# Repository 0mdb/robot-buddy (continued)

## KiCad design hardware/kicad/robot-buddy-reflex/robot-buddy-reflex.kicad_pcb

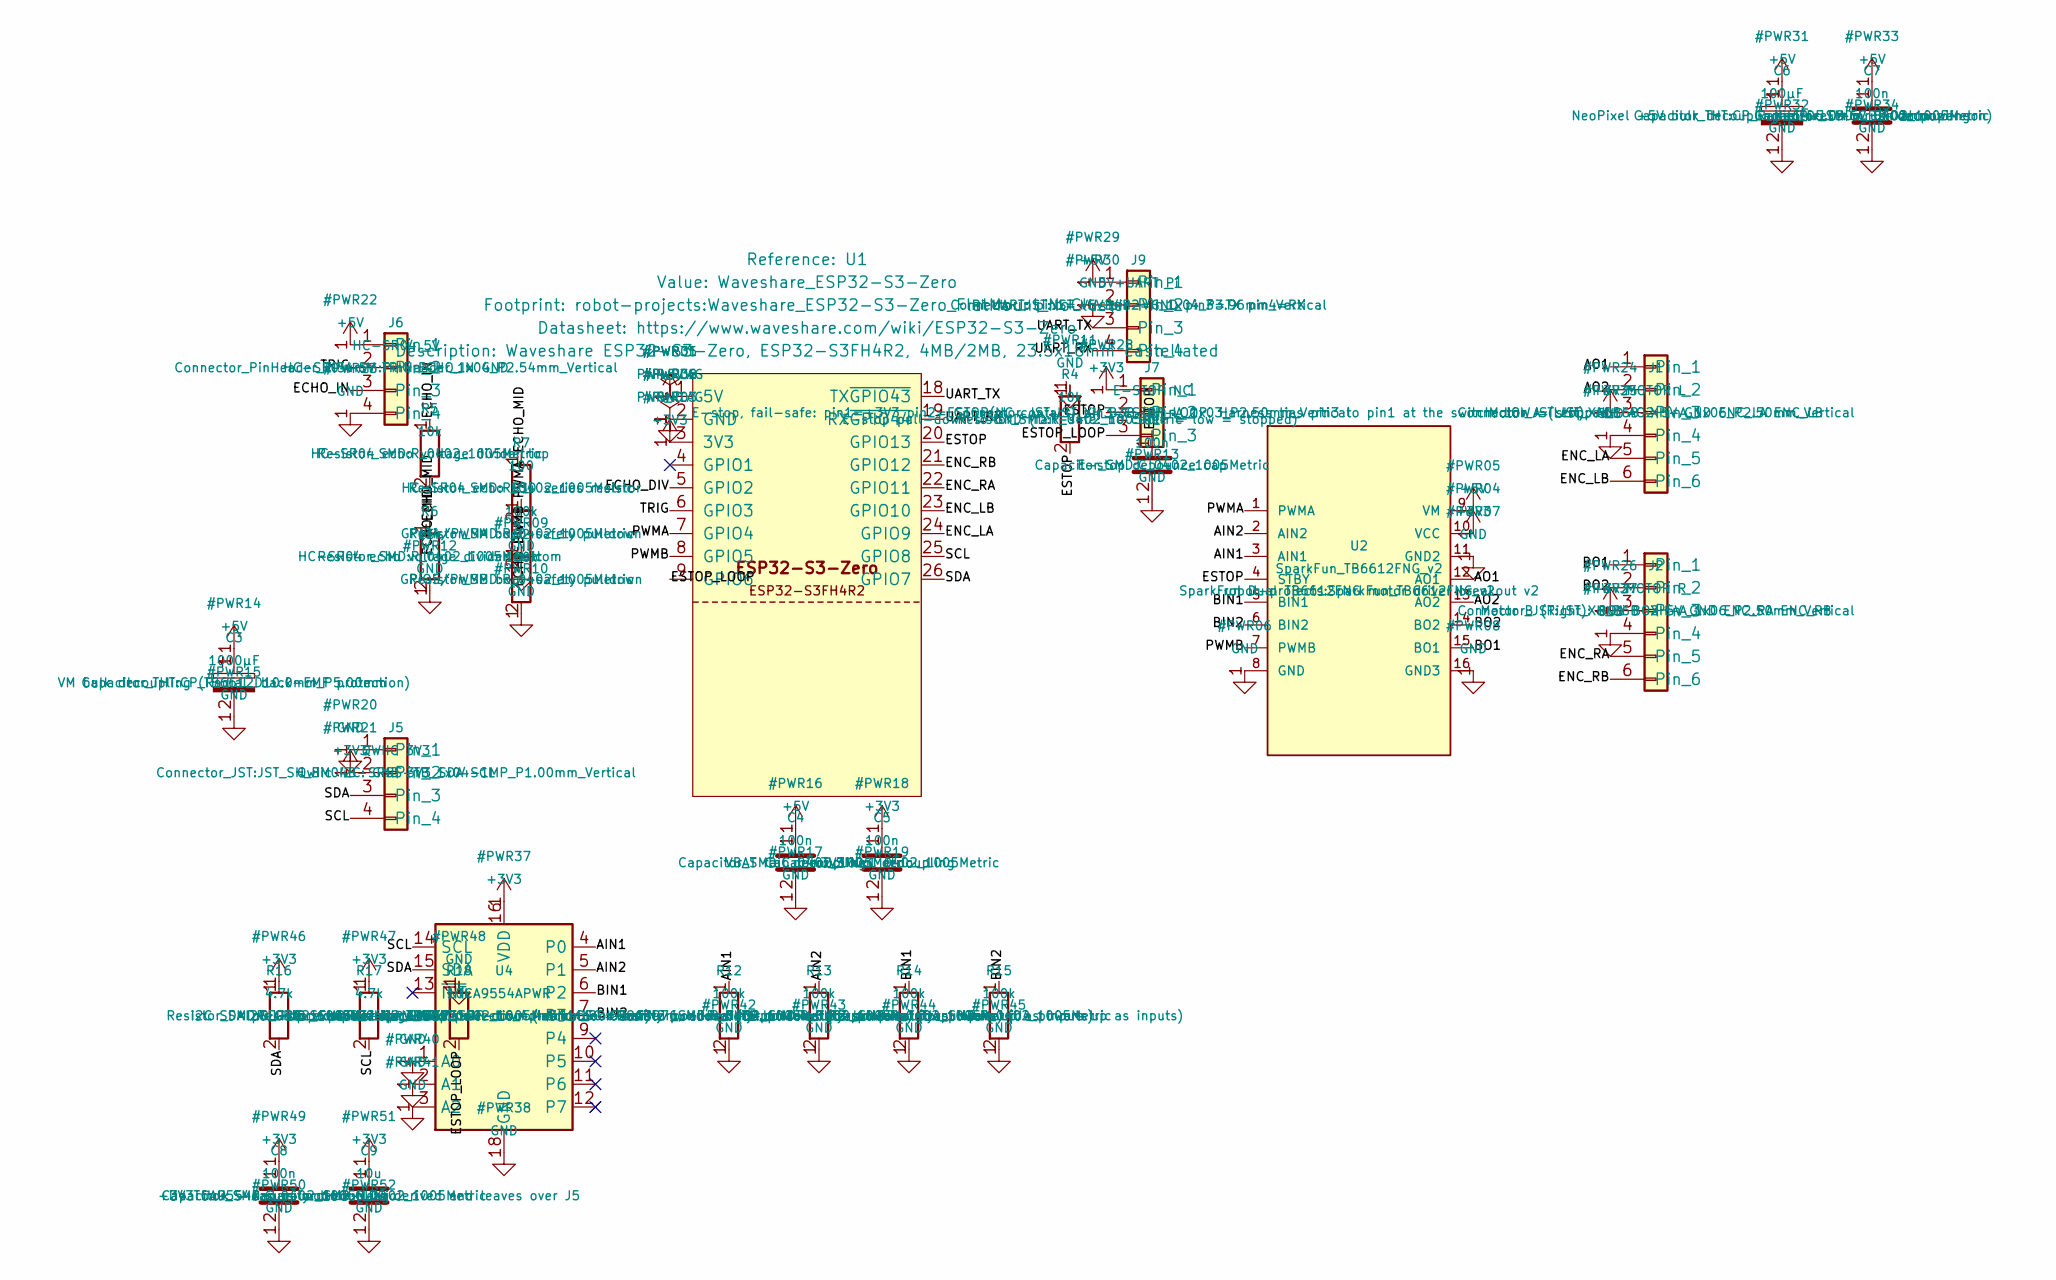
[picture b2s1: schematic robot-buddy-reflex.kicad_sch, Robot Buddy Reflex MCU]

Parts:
C1, C4, C5, C7, C8: 100n; C_0402_1005Metric
C3: 1000µF; CP_Radial_D10.0mm_P5.00mm
C6: 100µF; CP_Radial_D5.0mm_P2.00mm
C9: 10u; C_0402_1005Metric
J1: MOTOR L; JST_XH_B6B-XH-A_1x06_P2.50mm_Vertical
J2: MOTOR R; JST_XH_B6B-XH-A_1x06_P2.50mm_Vertical
J5: QWIIC 3V3; JST_SH_BM04B-SRSS-TB_1x04-1MP_P1.00mm_Vertical
J6: HC-SR04 5V; PinHeader_1x04_P2.54mm_Vertical
J7: E-STOP NC; JST_XH_B3B-XH-A_1x03_P2.50mm_Vertical
J9: 5V+UART Pi; JST_VH_B4P-VH_1x04_P3.96mm_Vertical
R1, R2, R12, R13, R14, R15: 100k; R_0402_1005Metric
R4, R5, R18: 10k; R_0402_1005Metric
R6: 15k; R_0402_1005Metric
R7: 100; R_0402_1005Metric
R16, R17: 4.7k; R_0402_1005Metric
U1: Waveshare_ESP32-S3-Zero; Waveshare_ESP32-S3-Zero_FlatMount_NoCluster
U2: SparkFun_TB6612FNG_v2
U4: TCA9554APWR; TSSOP-16_4.4x5mm_P0.65mm

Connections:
+3V3: C5.1, C8.1, C9.1, J1.3, J2.3, J5.2, J7.1, R16.1, R17.1, U1.3 (3V3), U2.10 (VCC), U4.16 (VDD)
/AIN1: R12.1, U2.3 (AIN1), U4.4 (P0)
/AIN2: R13.1, U2.2 (AIN2), U4.5 (P1)
/AO1: J1.1, U2.12 (AO1)
/AO2: J1.2, U2.13 (AO2)
/BIN1: R14.1, U2.5 (BIN1), U4.6 (P2)
/BIN2: R15.1, U2.6 (BIN2), U4.7 (P3)
/BO1: J2.1, U2.15 (BO1)
/BO2: J2.2, U2.14 (BO2)
/ECHO_DIV: R7.2, U1.5 (GPIO2)
/ECHO_IN: J6.3, R5.1
/ECHO_MID: R5.2, R6.1, R7.1
/ENC_LA: J1.5, U1.24 (GPIO9)
/ENC_LB: J1.6, U1.23 (GPIO10)
/ENC_RA: J2.5, U1.22 (GPIO11)
/ENC_RB: J2.6, U1.21 (GPIO12)
/ESTOP: C1.1, J7.2, R4.2, U1.20 (GPIO13), U2.4 (STBY)
/ESTOP_LOOP: J7.3, R18.2, U1.9 (GPIO6)
/PWMA: R1.1, U1.7 (GPIO4), U2.1 (PWMA)
/PWMB: R2.1, U1.8 (GPIO5), U2.7 (PWMB)
/SCL: J5.4, R17.2, U1.25 (GPIO8), U4.14 (SCL)
/SDA: J5.3, R16.2, U1.26 (GPIO7), U4.15 (SDA)
/TRIG: J6.2, U1.6 (GPIO3)
/UART_RX: J9.4, U1.19 (RX~GPIO44)
/UART_TX: J9.3, U1.18 (TX~GPIO43)

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
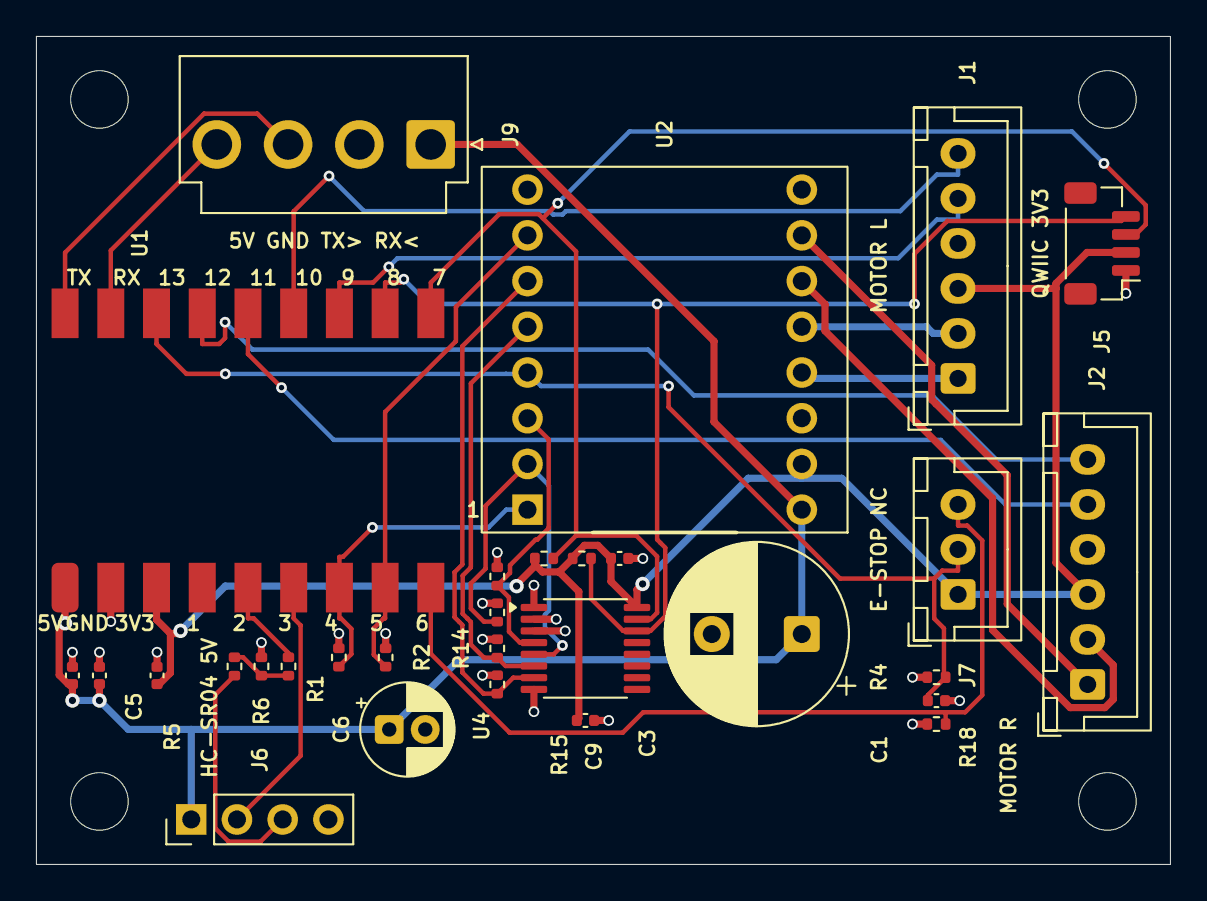
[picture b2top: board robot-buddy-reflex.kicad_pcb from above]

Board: 4 copper layers, 63.0 x 46.0 mm, 34 parts (0 on the bottom side), 27 nets.

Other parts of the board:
MH1, MH2, MH3, MH4: MountingHole; MountingHole_3.2mm_M3_DIN965

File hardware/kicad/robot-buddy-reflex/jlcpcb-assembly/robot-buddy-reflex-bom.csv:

Comment,Designator,Footprint,JLCPCB Part # (LCSC)
100,R7,R_0402_1005Metric,C25076
100k,"R1,R12,R13,R14,R15,R2",R_0402_1005Metric,C25741
100n,"C1,C4,C5,C7,C8",C_0402_1005Metric,C1525
10k,"R18,R4,R5",R_0402_1005Metric,C25744
10u,C9,C_0402_1005Metric,C15525
15k,R6,R_0402_1005Metric,C25756
4.7k,"R16,R17",R_0402_1005Metric,C25900
QWIIC 3V3,J5,JST_SH_BM04B-SRSS-TB_1x04-1MP_P1.00mm_Vertical,C160390
TCA9554APWR,U4,TSSOP-16_4.4x5mm_P0.65mm,C2863976

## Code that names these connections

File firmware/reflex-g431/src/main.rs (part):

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//!
//! Boards (Cargo feature): `board-nucleo` (default, bench) or `board-v3`. Pins:
//! `~/kicad-libs/docs/g431-pin-plan.md` (v3); the Nucleo moves three of them off the ST-LINK
//! VCP (USART2 on PA2/PA3), see README.md.
#![no_std]
#![no_main]
#![cfg_attr(feature = "bringup", allow(dead_code))]
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    config
}

/// ESTOP_N (PA6) closed loop = high. The pin is in AF mode for TIM1 BKIN; IDR still reads it.
fn estop_ok() -> bool {
    pac::GPIOA.idr().read().idr(6) == pac::gpio::vals::Idr::HIGH
}

/// PA6 -> TIM1_BKIN (AF6). Embassy checks the BreakInputPin trait but has no constructor for it.
fn route_bkin() {
    let pull = if cfg!(feature = "board-nucleo") {
        pac::gpio::vals::Pupdr::PULL_UP // nothing wired on the bench: loop "closed"
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        static mut TX: [u8; 256] = [0; 256];
        static mut RX: [u8; 256] = [0; 256];
        #[allow(static_mut_refs)]
        let uart = unsafe { BufferedUart::new(p.USART2, p.PA3, p.PA2, &mut TX, &mut RX, Irqs, ucfg) }.unwrap();
        (uart, p.PA10, p.PC7, p.PA1, p.PA7)
    };
    #[cfg(feature = "board-v3")]
    let (uart, ph_l, ph_r, isense_l, isense_r) = {
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        static mut TX: [u8; 256] = [0; 256];
        static mut RX: [u8; 256] = [0; 256];
        #[allow(static_mut_refs)]
        let uart = unsafe { BufferedUart::new(p.USART1, p.PA10, p.PA9, &mut TX, &mut RX, Irqs, ucfg) }.unwrap();
        (uart, p.PA2, p.PA7, p.PA1, p.PA3)
    };

    // ---- Motors: TIM1 CH1 (PA8) left EN, CH2N (PB0) right EN; COMP1/2 + BKIN -> break ----
    let ccfg = comp::Config { inverting_input: OC_THRESHOLD, hysteresis: Hysteresis::Hyst20M, ..Default::default() };
    let mut comp_l = Comp::new(p.COMP1, isense_l, Irqs, ccfg);
    let mut comp_r = Comp::new(p.COMP2, isense_r, Irqs, ccfg);
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    route_bkin();
    let pwm = ComplementaryPwm::new(
        p.TIM1,
        Some(PwmPin::new(p.PA8, OutputType::PushPull)),
        None,
        None,
        Some(ComplementaryPwmPin::new(p.PB0, OutputType::PushPull)),
        None,
        None,
        None,
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        pwm,
        Output::new(ph_l, Level::Low, Speed::Low),
        Output::new(ph_r, Level::Low, Speed::Low),
        Input::new(p.PC4, Pull::Up),
    );

    // ---- Encoders: TIM2 (PA5/PB3) left, TIM3 (PB4/PA4) right ----
    // Internal pull-ups as well as the encoder board's: a missing encoder reads still, not noise.
    let qcfg = {
        let mut c = embassy_stm32::timer::qei::Config::default();
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        c.ch2_pull = Pull::Up;
        c
    };
    let qei_l = Qei::new(p.TIM2, p.PA5, p.PB3, qcfg);
    let qei_r = Qei::new(p.TIM3, p.PB4, p.PA4, qcfg);
    // Input filter fDTS/16, N = 8: ~750 ns at 170 MHz (the ESP32 PCNT used a 1 µs glitch filter).
    for tim in [pac::TIM2.ccmr_input(0), pac::TIM3.ccmr_input(0)] {
        tim.modify(|w| {
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        });
    }

    // ---- IMU: LSM6DSV16X on SPI2 (PB13 SCK, PB15 MOSI, PB14 MISO, PB12 CS) ----
    let mut scfg = spi::Config::default();
    scfg.mode = spi::MODE_3;
    scfg.frequency = mhz(8);
    let spi = Spi::new_blocking(p.SPI2, p.PB13, p.PB15, p.PB14, scfg);
    let mut imu = imu::Imu::new(spi, Output::new(p.PB12, Level::High, Speed::VeryHigh));
    let imu = if imu.init(&cfg) {
        info!("imu: LSM6DSV16X up");
        Some(imu)
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        None
    };

    // ---- Sonars: TIM4 capture at 1 MHz, front echo PA11 (CH1), rear PB9 (CH4) ----
    let ic = InputCapture::new(
        p.TIM4,
        Some(CapturePin::new(p.PA11, Pull::None)),
        None,
        None,
        Some(CapturePin::new(p.PB9, Pull::None)),
        Irqs,
        mhz(1),
        CountingMode::EdgeAlignedUp,
    );
    let sonar = sonar::Sonar::new(
        ic,
        Output::new(p.PC10, Level::Low, Speed::Low),
        Output::new(p.PC11, Level::Low, Speed::Low),
    );

    let led = Output::new(p.PC6, Level::Low, Speed::Low);

    // Motors are enabled at boot; the safety task gates them on faults (app_main.cpp).
    let mut motors = motors;
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
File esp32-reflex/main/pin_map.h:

#pragma once
// GPIO assignments — Reflex MCU (Waveshare ESP32-S3-Zero on robot-buddy-reflex v2).
// All pin choices in one place. Must match the board: hardware/kicad/pcb_qc.py §3
// checks every PIN_* here against the schematic netlist.
//
// v2 board (docs/v2-defect-register.md §A0, §M11): the module is soldered flat with its
// PERIMETER pads only (no underside cluster), so GPIO17/18/38/39 are gone. The four
// TB6612 direction lines moved to a TCA9554A I²C expander (U4), and TB6612 STBY is tied
// to the hardware e-stop net, not to a GPIO.

#include "driver/gpio.h"

#include <cstdint>

// ---- Motor driver (TB6612FNG) ----
// PWM outputs (LEDC channels). U1 pads 7/8. R1/R2 100k pull-downs hold them low at boot.
constexpr gpio_num_t PIN_PWMA = GPIO_NUM_4; // left motor PWM
constexpr gpio_num_t PIN_PWMB = GPIO_NUM_5; // right motor PWM

// Direction lines are TCA9554A port bits, not GPIOs (U4: P0-P3 = U4 pins 4-7).
// The expander powers up with every port an input; R12-R15 100k pull-downs hold all
// four lines low until firmware drives them (register A2: power-up state is a safety
// property). Set a direction only through motor.cpp, which sequences PWM around it.
constexpr uint8_t EXP_I2C_ADDR = 0x38;    // TCA9554A, A2..A0 = GND
constexpr uint8_t EXP_BIT_AIN1 = 1u << 0; // P0: left fwd
constexpr uint8_t EXP_BIT_AIN2 = 1u << 1; // P1: left rev
constexpr uint8_t EXP_BIT_BIN1 = 1u << 2; // P2: right fwd
constexpr uint8_t EXP_BIT_BIN2 = 1u << 3; // P3: right rev
constexpr uint8_t EXP_DIR_MASK = 0x0F;    // P4-P7 unconnected (stay inputs)

// ---- Encoders (quadrature, directly to PCNT) ----
// Powered from +3V3 on v2 (register M7): A/B are 3.3 V logic into these pins.
constexpr gpio_num_t PIN_ENC_L_A = GPIO_NUM_9;
constexpr gpio_num_t PIN_ENC_L_B = GPIO_NUM_10;
constexpr gpio_num_t PIN_ENC_R_A = GPIO_NUM_11;
constexpr gpio_num_t PIN_ENC_R_B = GPIO_NUM_12;

// ---- Shared I²C bus: BMI270 IMU (via Qwiic J5) + TCA9554A expander (U4) ----
// U1 pads 26/25. R16/R17 4.7k pull-ups to +3V3 on the board. One bus, owned by
// i2c_bus.cpp; both devices hang off it.
constexpr gpio_num_t PIN_I2C_SDA = GPIO_NUM_7;
constexpr gpio_num_t PIN_I2C_SCL = GPIO_NUM_8;
// Names the IMU code (and pcb_qc.py) use for the same two pins.
constexpr gpio_num_t PIN_IMU_SDA = PIN_I2C_SDA;
constexpr gpio_num_t PIN_IMU_SCL = PIN_I2C_SCL;

// ---- Ultrasonic range sensor (HC-SR04) ----
constexpr gpio_num_t PIN_RANGE_TRIG = GPIO_NUM_3; // output: 10 µs trigger pulse
constexpr gpio_num_t PIN_RANGE_ECHO = GPIO_NUM_2; // input: echo via the R5/R6 divider

// ---- E-stop (register E3: fail-safe, with cable detect) ----
// /ESTOP: +3V3 through the NC contact. HIGH = switch intact, robot may run.
// LOW = stopped (pressed or cable missing; R4 pulls it down). The same net drives TB6612
// STBY directly, so the hardware kill needs no firmware; this pin is for reporting.
constexpr gpio_num_t PIN_ESTOP_N = GPIO_NUM_13; // active-low, external pull-DOWN (R4)
// /ESTOP_LOOP: J7 pin 3, tied to pin 1 (+3V3) at the switch in the harness.
// HIGH = cable present; LOW = cable missing (R18 pull-down).
constexpr gpio_num_t PIN_ESTOP_LOOP = GPIO_NUM_6;

// Battery voltage sense is Pi-side (Waveshare UPS HAT (B) INA219 over I²C), see
// docs/power.md. GPIO1 (U1 pad 4) is free.
